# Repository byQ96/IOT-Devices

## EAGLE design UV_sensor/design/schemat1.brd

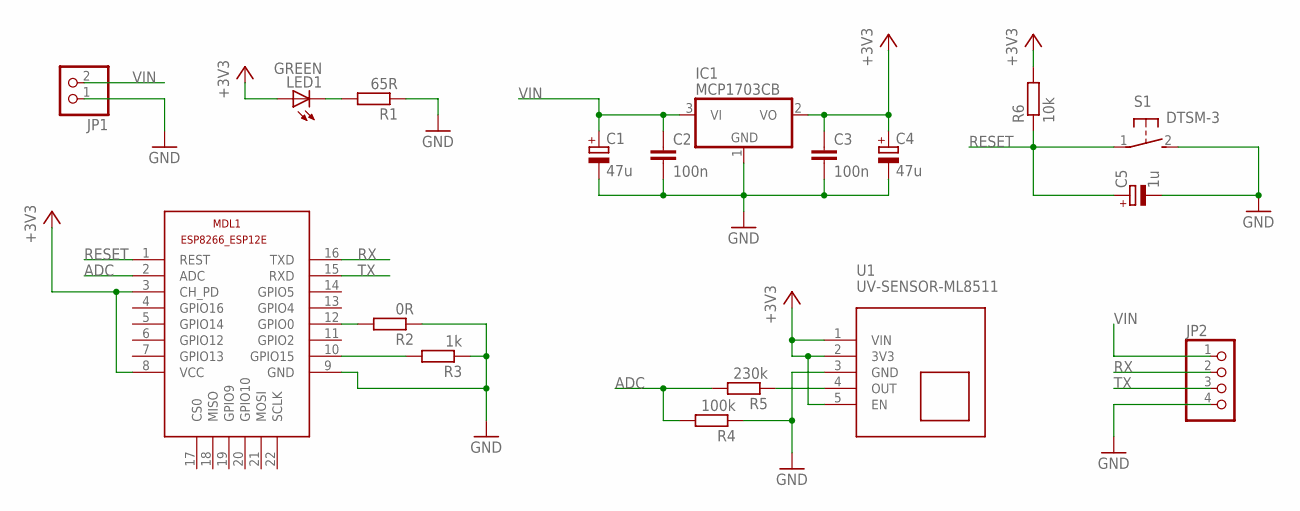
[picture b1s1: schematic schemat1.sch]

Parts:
C1, C4: 47u; CT3528
C2, C3: 100n; C0805
C5: 1u; CT3216
IC1: MCP1703CB; SOT23
JP1: PINHD-1X2; 1X02
JP2: PINHD-1X4/90; 1X04/90
LED1: GREEN; LED_1206
MDL1: ESP8266-12EESP8266-ESP12E; ESP8266-ESP12E
R1: 65R; R0805
R2: 0R; R0805
R3: 1k; R0805
R4: 100k; R0805
R5: 230k; R0805
R6: 10k; R0805
S1: DTSM-3
U1: UV-SENSOR-ML8511

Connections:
+3V3: C3.1, C4.+, IC1.2 (VO), LED1.A, MDL1.3 (CH_PD), MDL1.8 (VCC), R6.2, U1.1 (VIN), U1.2 (3V3), U1.5 (EN)
ADC: MDL1.2 (ADC), R4.2, R5.2
GND: C1.-, C2.2, C3.2, C4.-, C5.-, IC1.1 (GND), JP1.1, JP2.4, MDL1.9 (GND), R1.1, R2.1, R3.1, R4.1, S1.2, U1.3 (GND)
unnamed: R5.1, U1.4 (OUT)
unnamed: LED1.C, R1.2
unnamed: MDL1.12 (GPIO0), R2.2
unnamed: MDL1.10 (GPIO15), R3.2
RESET: C5.+, MDL1.1 (REST), R6.1, S1.1
RX: JP2.2, MDL1.16 (TXD)
TX: JP2.3, MDL1.15 (RXD)
VIN: C1.+, C2.1, IC1.3 (VI), JP1.2, JP2.1

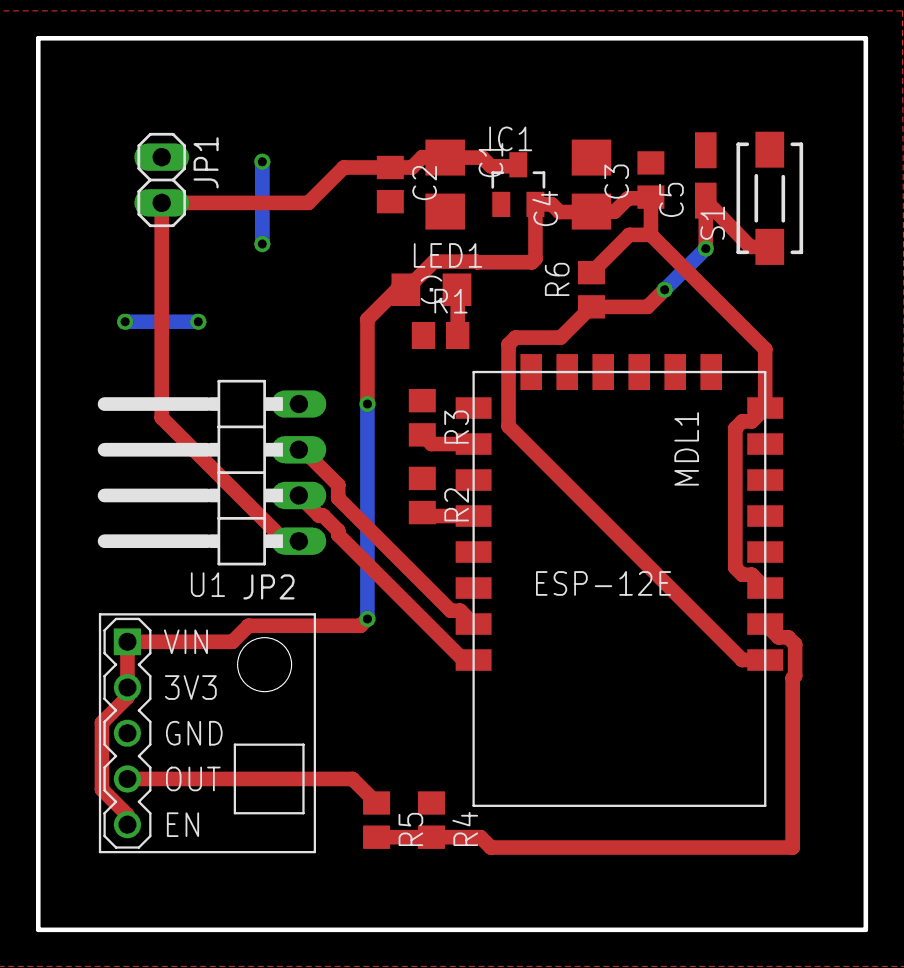
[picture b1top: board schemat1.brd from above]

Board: 2 copper layers, 46.0 x 49.5 mm, 18 parts (0 on the bottom side), 11 nets.

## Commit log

2017-11-13 Uv sensor reeady scheme

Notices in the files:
parts and their libraries:
diy-modules: Released under the Creative Commons Attribution 4.0 International License: http://creativecommons.org/licenses/by/4.0
